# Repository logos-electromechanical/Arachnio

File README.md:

# Arachnio
An Arduino Micro variant with integrated WiFi

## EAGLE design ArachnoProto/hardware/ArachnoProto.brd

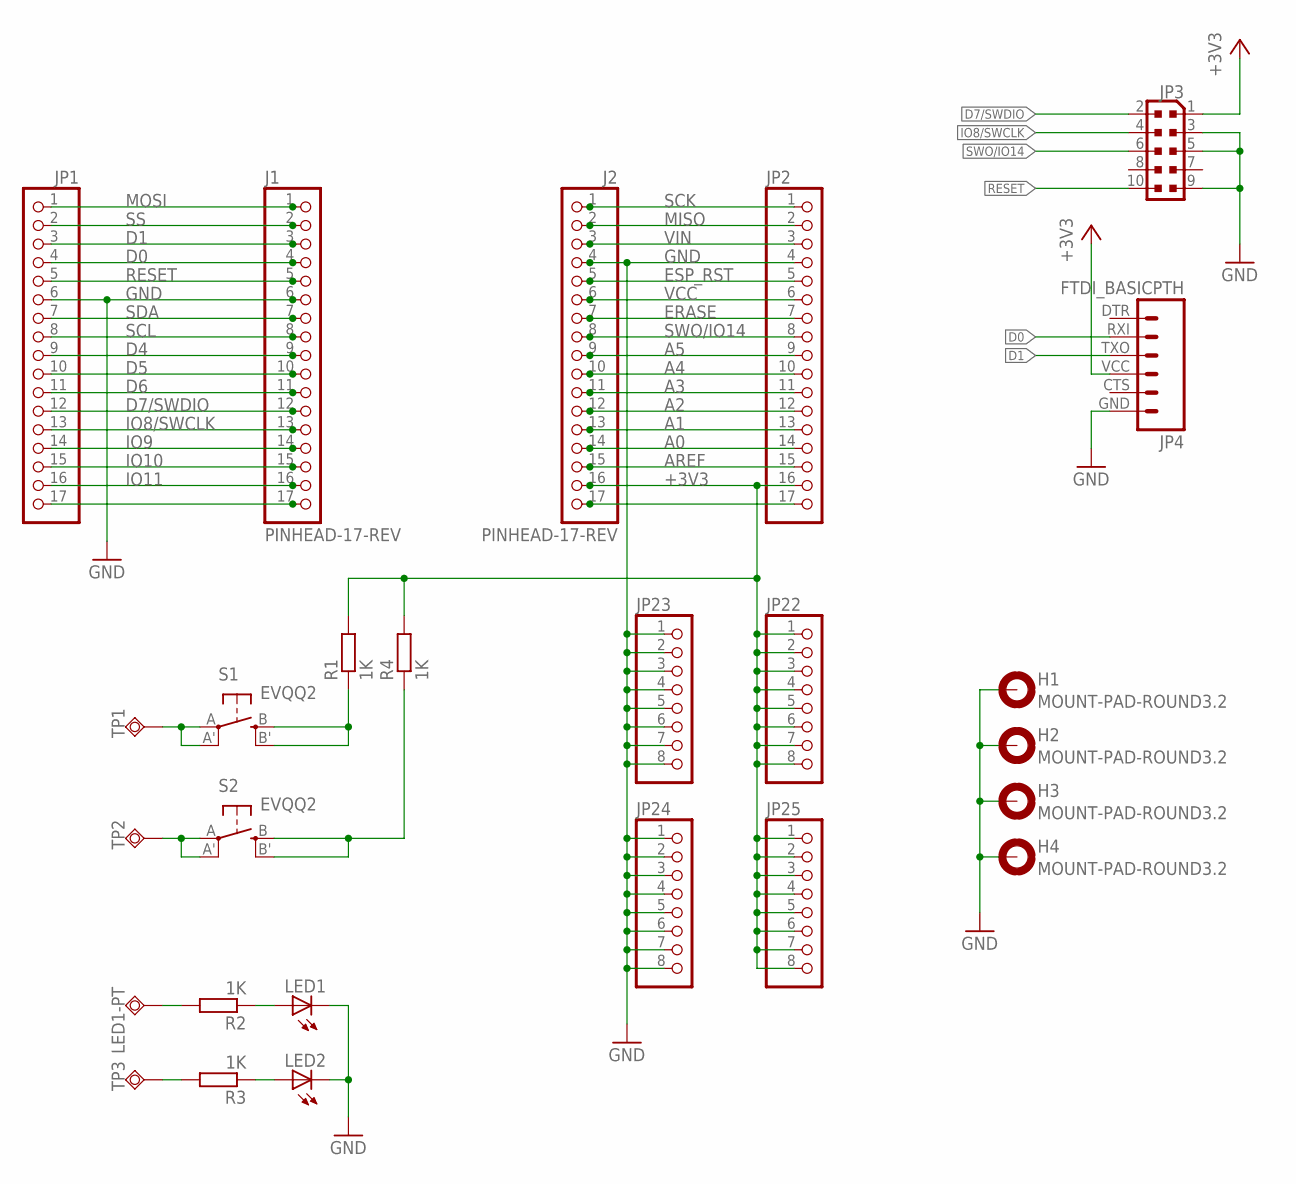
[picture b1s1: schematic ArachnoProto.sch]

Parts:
H1, H2, H3, H4: MOUNT-PAD-ROUND3.2; 3,2-PAD
J1, J2: PINHEAD-17-REV; 4UCONN-12573
JP1, JP2: PINHD-1X17; 1X17
JP3: PINHEAD_PINHD-2X5PASSO127; PINHEAD_2X05_127
JP4: FTDI_BASICPTH; FTDI_BASIC
JP22, JP23, JP24, JP25: PINHD-1X8; 1X08
LED1, LED2: LEDCHIPLED_1206; CHIPLED_1206
LED1-PT: TPSQPAD1-20Y; P1-20Y
R1, R2, R3, R4: 1K; R1206
S1, S2: EVQQ2; EVQ-Q2
TP1, TP2, TP3: TPSQPAD1-20Y; P1-20Y

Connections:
+3V3: J2.16, J2.33, J2.50, JP2.16, JP3.1, JP4.VCC (4), JP22.1, JP22.2, JP22.3, JP22.4, JP22.5, JP22.6, JP22.7, JP22.8, JP25.1, JP25.2, JP25.3, JP25.4, JP25.5, JP25.6, JP25.7, JP25.8, R1.2, R4.2
A0: J2.14, J2.31, J2.48, JP2.14
A1: J2.13, J2.30, J2.47, JP2.13
A2: J2.12, J2.29, J2.46, JP2.12
A3: J2.11, J2.28, J2.45, JP2.11
A4: J2.10, J2.27, J2.44, JP2.10
A5: J2.9, J2.26, J2.43, JP2.9
AREF: J2.15, J2.32, J2.49, JP2.15
D0: J1.4, J1.21, J1.38, JP1.4, JP4.RXI (2)
D1: J1.3, J1.20, J1.37, JP1.3, JP4.TXO (3)
D4: J1.9, J1.26, J1.43, JP1.9
D5: J1.10, J1.27, J1.44, JP1.10
D6: J1.11, J1.28, J1.45, JP1.11
D7/SWDIO: J1.12, J1.29, J1.46, JP1.12, JP3.2
ERASE: J2.7, J2.24, J2.41, JP2.7
ESP_RST: J2.5, J2.22, J2.39, JP2.5
GND: H1.B3,2, H2.B3,2, H3.B3,2, H4.B3,2, J1.6, J1.23, J1.40, J2.4, J2.21, J2.38, JP1.6, JP2.4, JP3.3, JP3.5, JP3.9, JP4.GND (6), JP23.1, JP23.2, JP23.3, JP23.4, JP23.5, JP23.6, JP23.7, JP23.8, JP24.1, JP24.2, JP24.3, JP24.4, JP24.5, JP24.6, JP24.7, JP24.8, LED1.C, LED2.C
IO8/SWCLK: J1.13, J1.30, J1.47, JP1.13, JP3.4
IO9: J1.14, J1.31, J1.48, JP1.14
IO10: J1.15, J1.32, J1.49, JP1.15
IO11: J1.16, J1.33, J1.50, JP1.16
IO12: J1.17, J1.34, J1.51, JP1.17
IO13: J2.17, J2.34, J2.51, JP2.17
MISO: J2.2, J2.19, J2.36, JP2.2
MOSI: J1.1, J1.18, J1.35, JP1.1
unnamed: LED1.A, R2.1
unnamed: LED2.A, R3.1
unnamed: LED1-PT.TP, R2.2
unnamed: R3.2, TP3.TP
unnamed: S1.A, S1.A' (P1), TP1.TP
unnamed: R1.1, S1.B (S), S1.B' (S1)
unnamed: R4.1, S2.B (S), S2.B' (S1)
unnamed: S2.A, S2.A' (P1), TP2.TP
RESET: J1.5, J1.22, J1.39, JP1.5, JP3.10
SCK: J2.1, J2.18, J2.35, JP2.1
SCL: J1.8, J1.25, J1.42, JP1.8
SDA: J1.7, J1.24, J1.41, JP1.7
SS: J1.2, J1.19, J1.36, JP1.2
SWO/IO14: J2.8, J2.25, J2.42, JP2.8, JP3.6
VCC: J2.6, J2.23, J2.40, JP2.6
VIN: J2.3, J2.20, J2.37, JP2.3

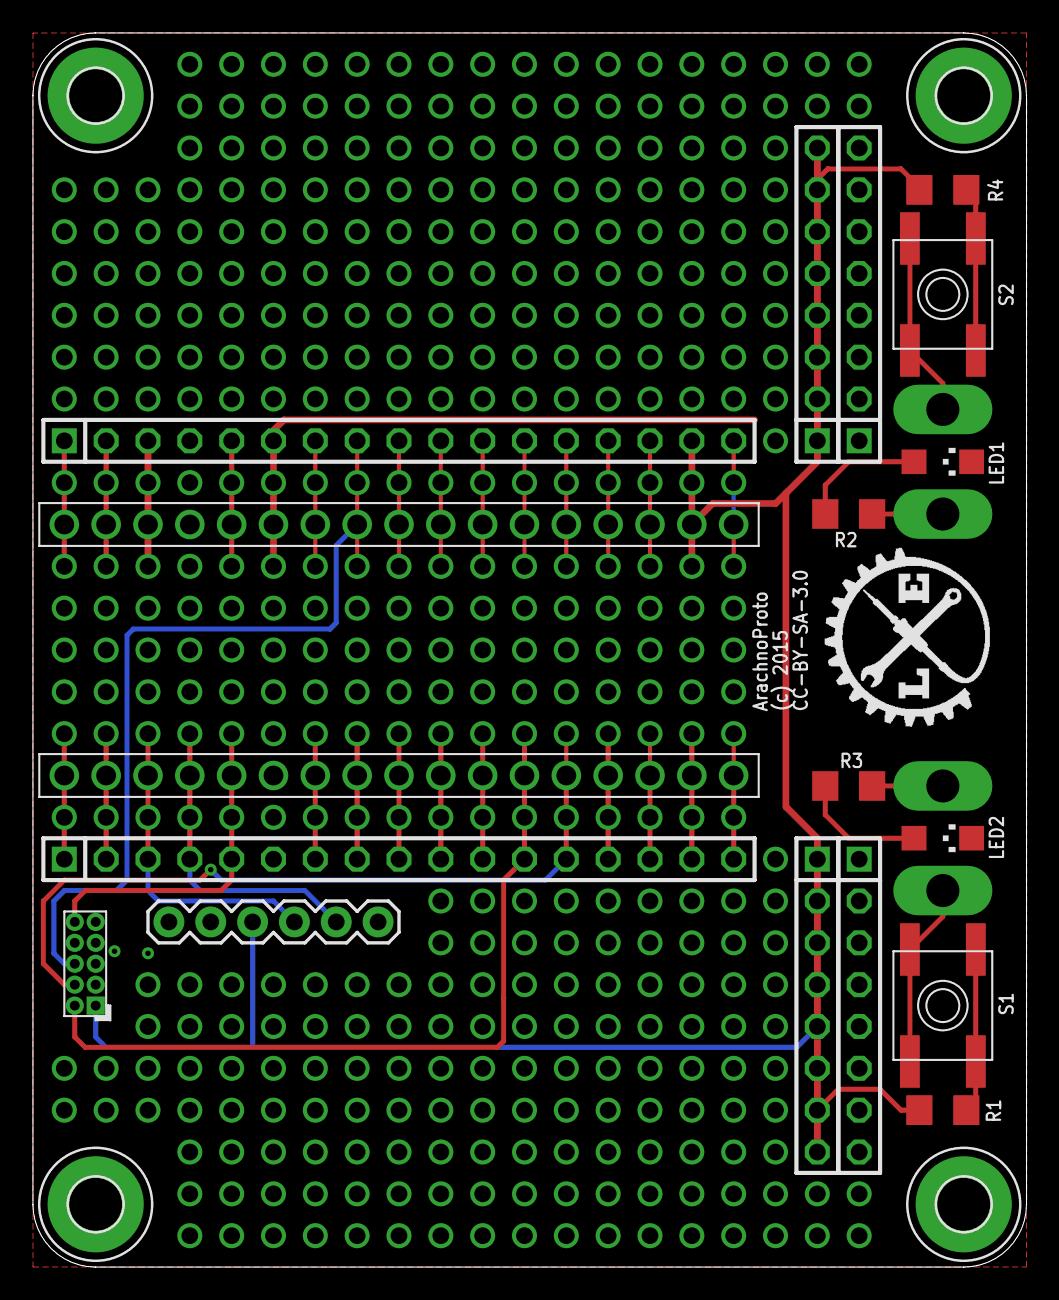
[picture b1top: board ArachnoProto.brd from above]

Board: 2 copper layers, 60.3 x 74.9 mm, 27 parts (0 on the bottom side), 41 nets.

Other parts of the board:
U$1: LOGO-SM

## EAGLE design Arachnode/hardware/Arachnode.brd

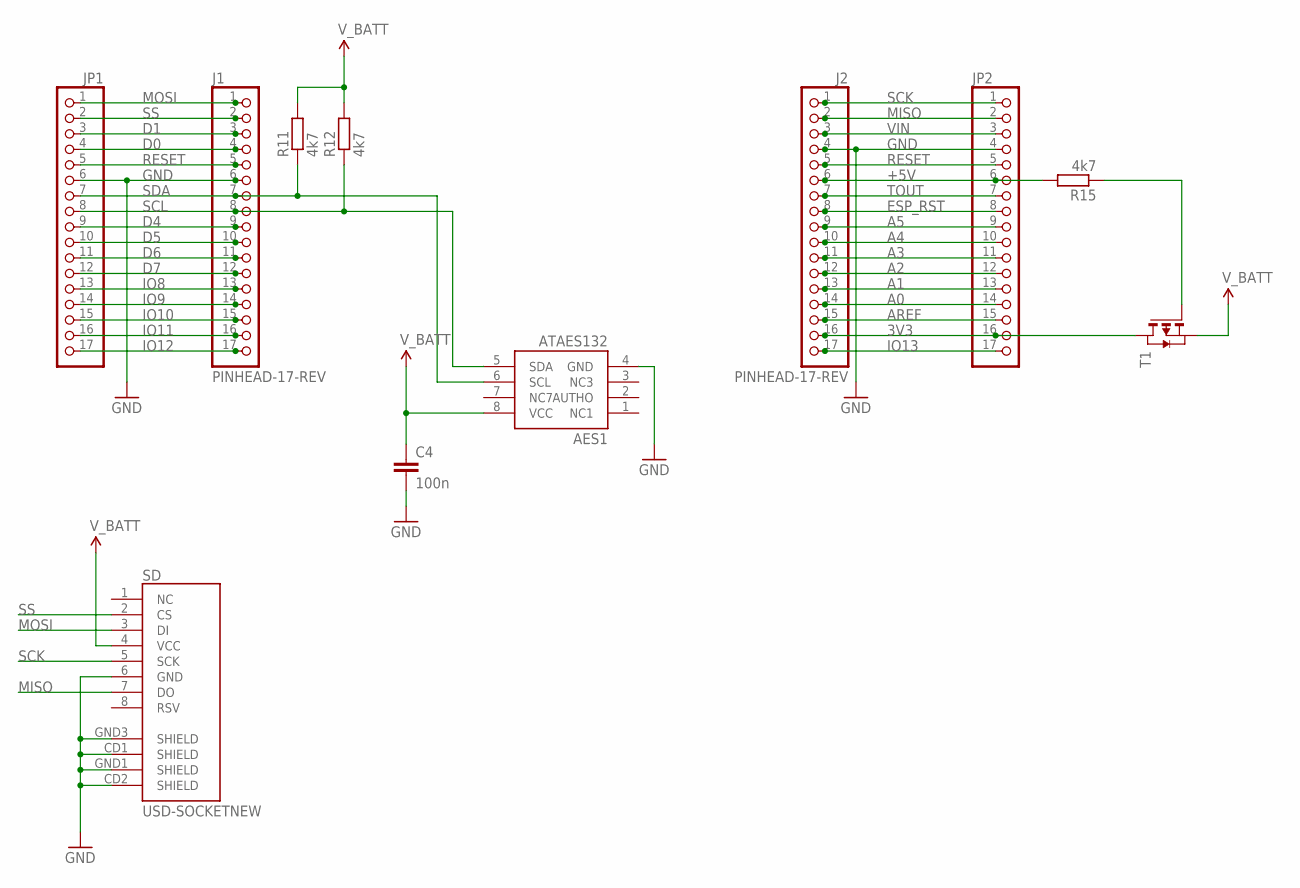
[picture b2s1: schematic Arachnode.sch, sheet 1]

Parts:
AES1: ATAES132; SOIC8
C4: 100n; C0603
J1, J2: PINHEAD-17-REV; 4UCONN-12573
JP1, JP2: PINHD-1X17_2.54; 1X17
R11, R12, R15: 4k7; R0603
SD: USD-SOCKETNEW; MICRO-SD-SOCKET-PP; PARTNO 502570-0893
T1: PMOSSOT23; SOT-23

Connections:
3V3: J2.16, J2.33, J2.50, JP2.16, T1.1 (D)
+5V: J2.6, J2.23, J2.40, JP2.6, R15.2
A0: J2.14, J2.31, J2.48, JP2.14; also elsewhere on the board
A1: J2.13, J2.30, J2.47, JP2.13; also elsewhere on the board
A2: J2.12, J2.29, J2.46, JP2.12
A3: J2.11, J2.28, J2.45, JP2.11
A4: J2.10, J2.27, J2.44, JP2.10
A5: J2.9, J2.26, J2.43, JP2.9
AREF: J2.15, J2.32, J2.49, JP2.15
D0: J1.4, J1.21, J1.38, JP1.4
D1: J1.3, J1.20, J1.37, JP1.3
D4: J1.9, J1.26, J1.43, JP1.9
D5: J1.10, J1.27, J1.44, JP1.10
D6: J1.11, J1.28, J1.45, JP1.11
D7: J1.12, J1.29, J1.46, JP1.12
ESP_RST: J2.8, J2.25, J2.42, JP2.8
GND: AES1.4 (GND), C4.2, J1.6, J1.23, J1.40, J2.4, J2.21, J2.38, JP1.6, JP2.4, SD.6 (GND), SD.CD1 (SHIELD), SD.CD2 (SHIELD), SD.GND1 (SHIELD), SD.GND3 (SHIELD); also elsewhere on the board
IO8: J1.13, J1.30, J1.47, JP1.13
IO9: J1.14, J1.31, J1.48, JP1.14
IO10: J1.15, J1.32, J1.49, JP1.15
IO11: J1.16, J1.33, J1.50, JP1.16
IO12: J1.17, J1.34, J1.51, JP1.17
IO13: J2.17, J2.34, J2.51, JP2.17
MISO: J2.2, J2.19, J2.36, JP2.2, SD.7 (DO)
MOSI: J1.1, J1.18, J1.35, JP1.1, SD.3 (DI)
unnamed: R15.1, T1.3 (G)
RESET: J1.5, J1.22, J1.39, J2.5, J2.22, J2.39, JP1.5, JP2.5
SCK: J2.1, J2.18, J2.35, JP2.1, SD.5 (SCK)
SCL: AES1.5 (SDA), J1.8, J1.25, J1.42, JP1.8, R12.1
SDA: AES1.6 (SCL), J1.7, J1.24, J1.41, JP1.7, R11.1
SS: J1.2, J1.19, J1.36, JP1.2, SD.2 (CS)
TOUT: J2.7, J2.24, J2.41, JP2.7
VIN: J2.3, J2.20, J2.37, JP2.3; also elsewhere on the board
V_BATT: AES1.8 (VCC), C4.1, R11.2, R12.2, SD.4 (VCC), T1.2 (S); also elsewhere on the board

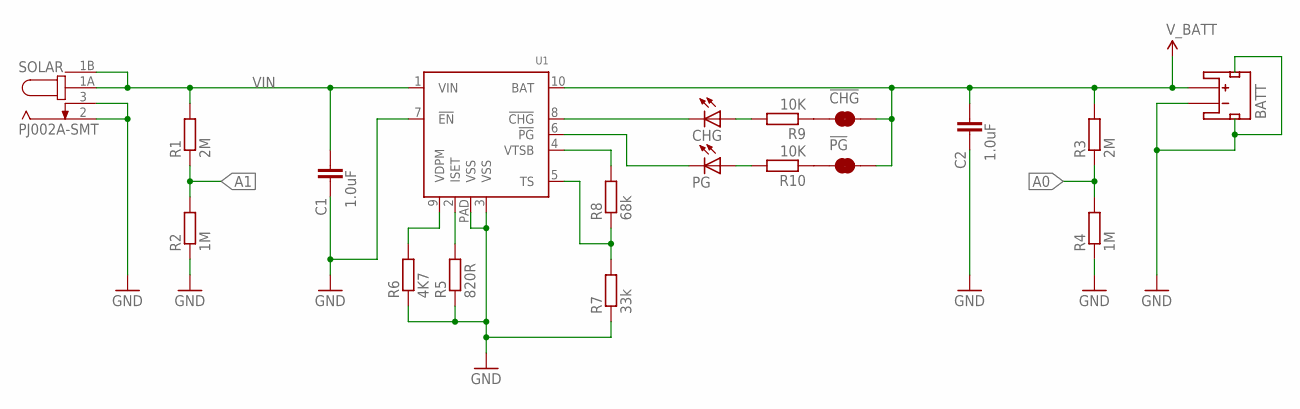
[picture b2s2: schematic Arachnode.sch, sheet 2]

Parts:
!CHG!: JUMPER-PAD-2-NC_BY_TRACE; PAD-JUMPER-2-NC_BY_TRACE_YES_SILK
!PG!: JUMPER-PAD-2-NC_BY_TRACE; PAD-JUMPER-2-NC_BY_TRACE_YES_SILK
BATT: JST_2MM_MALE; JST-2-SMD; PARTNO S2B-PH-SM4-TB(LF)(SN)
C1, C2: 1.0uF; C0603
CHG: LEDCHIP-LED0603; CHIP-LED0603
PG: LEDCHIP-LED0603; CHIP-LED0603
R1, R3: 2M; R0603
R2, R4: 1M; R0603; PARTNO ERJ-3EKF1004V
R5: 820R; R0603
R6: 4K7; R0603
R7: 33k; R0603
R8: 68k; R0603
R9, R10: 10K; R0603
SOLAR: PJ002A-SMT; PARTNO PJ-002AH-SMT
U1: BQ24210; WSON-10

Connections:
A0: R3.1, R4.2; also elsewhere on the board
A1: R1.1, R2.2; also elsewhere on the board
GND: BATT.1 (-), BATT.NC1 (PAD1), BATT.NC2 (PAD2), C1.1, C2.1, R2.1, R4.1, R5.1, R6.1, R7.1, SOLAR.2, SOLAR.3, U1.3 (VSS), U1.7 (!EN!), U1.PAD (VSS); also elsewhere on the board
unnamed: PG.A, R10.2
unnamed: R5.2, U1.2 (ISET)
unnamed: CHG.A, R9.2
unnamed: R6.2, U1.9 (VDPM)
unnamed: R7.2, R8.1, U1.5 (TS)
unnamed: PG.C, U1.6 (!PG!)
unnamed: R8.2, U1.4 (VTSB)
unnamed: CHG.C, U1.8 (!CHG!)
unnamed: !CHG!.1, R9.1
unnamed: !PG!.1, R10.1
VIN: C1.2, R1.2, SOLAR.1A, SOLAR.1B, U1.1 (VIN); also elsewhere on the board
V_BATT: !CHG!.2, !PG!.2, BATT.2 (+), C2.2, R3.2, U1.10 (BAT); also elsewhere on the board

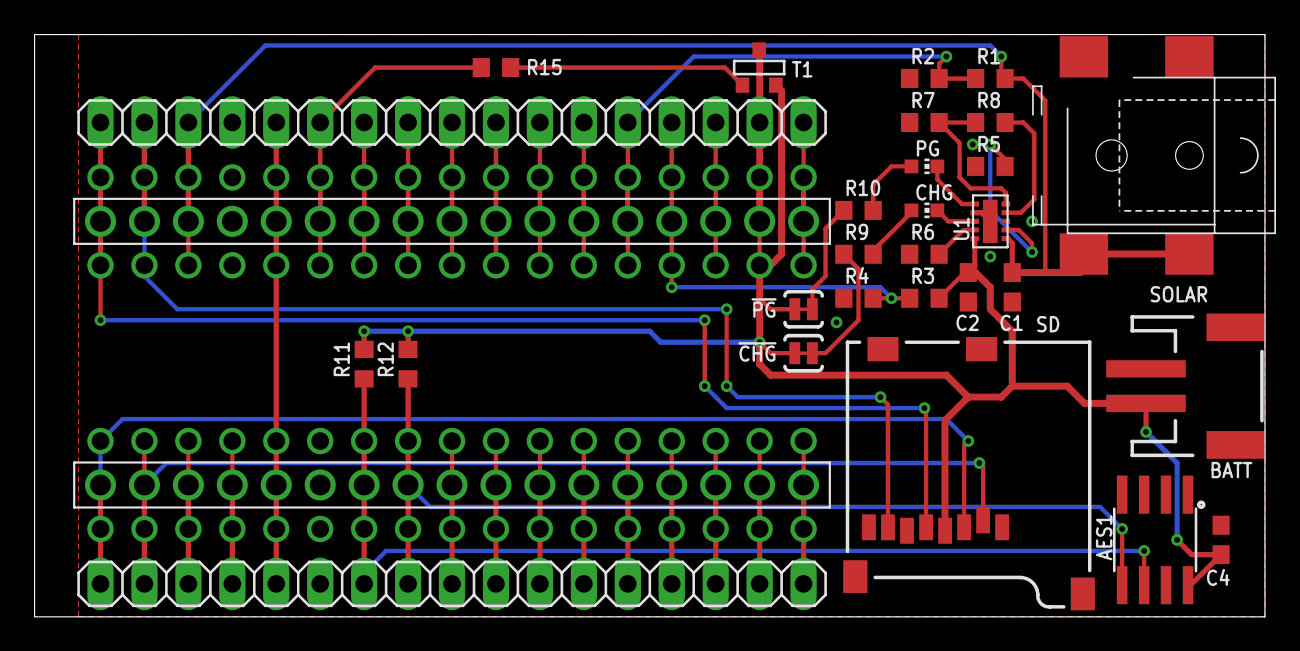
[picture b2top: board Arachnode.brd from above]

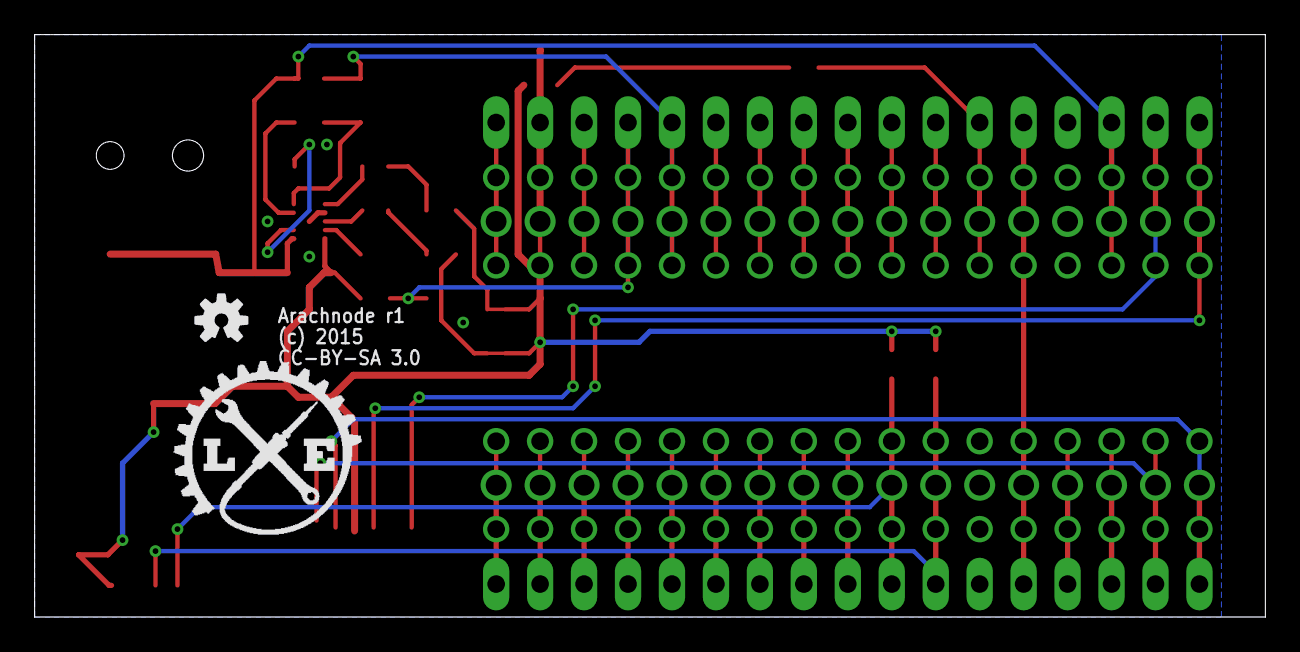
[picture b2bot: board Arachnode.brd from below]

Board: 2 copper layers, 71.1 x 33.7 mm, 32 parts (2 on the bottom side), 44 nets.

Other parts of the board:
U$1: OSHW-LOGO-S
U$2: LOGO-SM

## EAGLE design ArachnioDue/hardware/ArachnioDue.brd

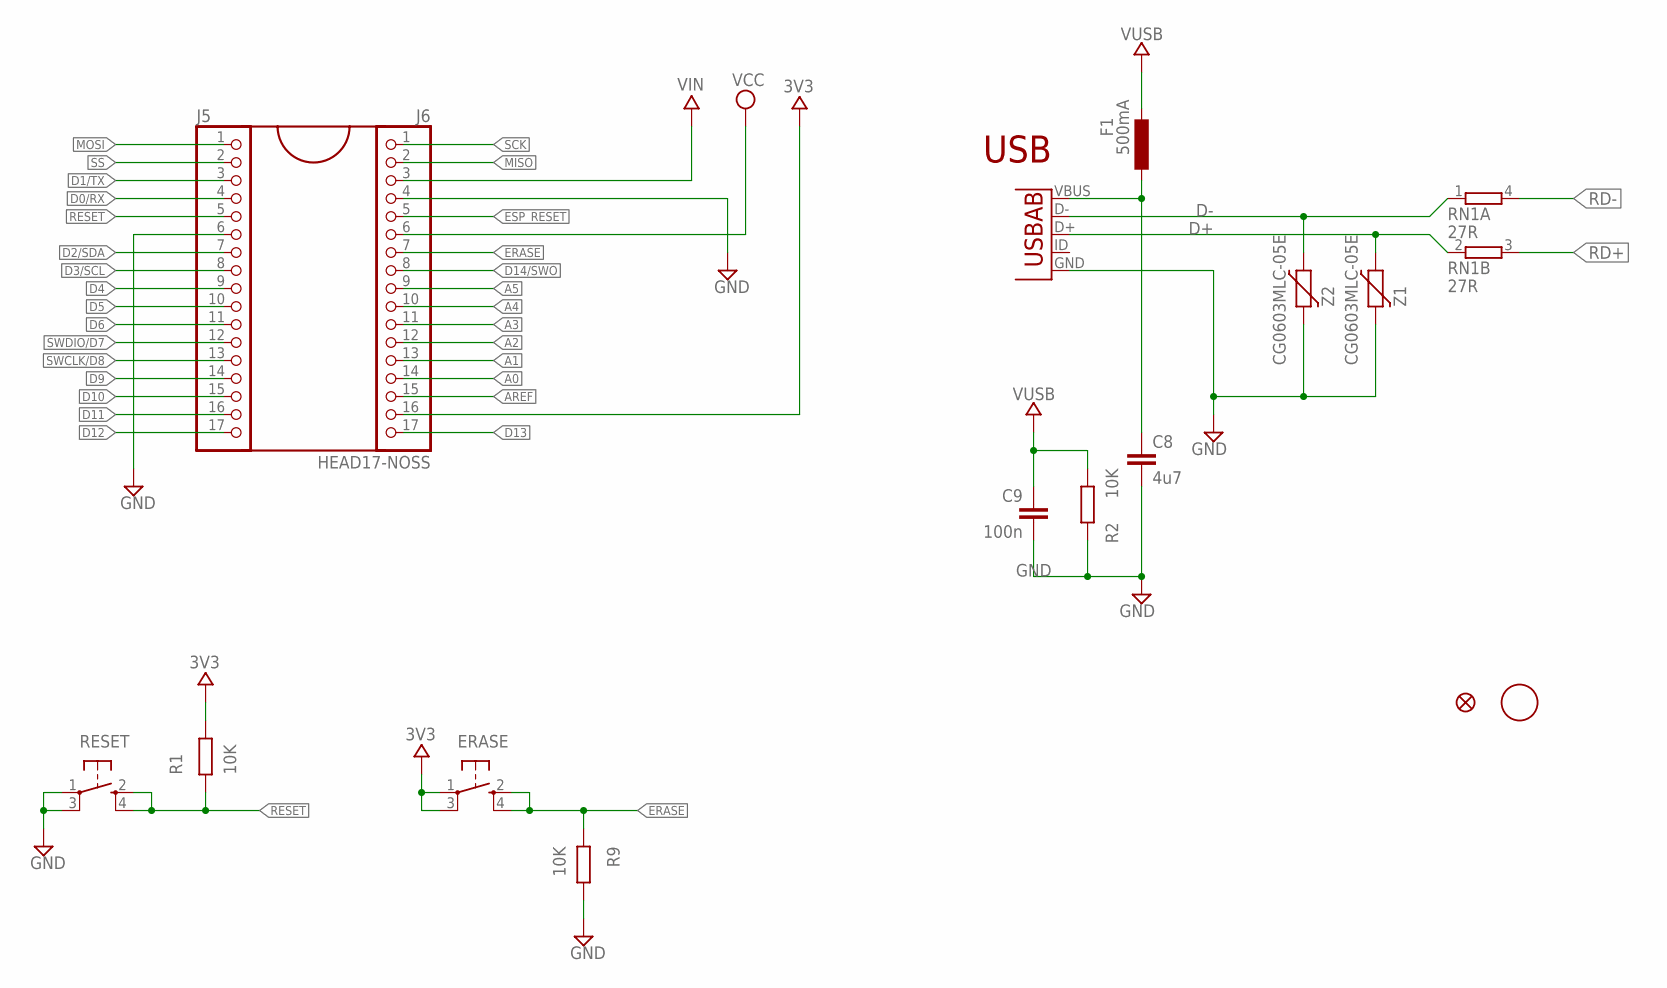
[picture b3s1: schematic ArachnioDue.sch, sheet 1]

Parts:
C8: 4u7; C0603; PARTNO generic MLCC:4u7/25V/0603
C9: 100n; C0603; PARTNO generic MLCC:100n/50V/0603
CN1: USB-AB; USB-AB-MICRO-SMD; PARTNO 10104111-0001LF
ERASE: SPST_TACT-KMR2; KMR2; PARTNO KMR221NG
F1: 500mA; L1812; PARTNO MF-MSMF050-2
J5: PINHD-1X17_2.54-SMD-UNIVERSAL; 1X17SMD-UNIVERSAL; PARTNO PREC017SAAN-RC
J6: HEAD17-NOSS; 1X17SMD-UNIVERSAL; PARTNO PREC017SAAN-RC
R1, R2, R9: 10K; R0402; PARTNO generic resistor:10K/0402
RESET: SPST_TACT-KMR2; KMR2; PARTNO KMR221NG
RN1: 27R; EXBV4V; PARTNO EXB-V4V270JV
U$37: FIDUCIALMOUNT; FIDUCIA-MOUNT
U$53: FIDUCIAL1X2; FIDUCIAL-1X2
Z1, Z2: CG0603MLC-05E; CT/CN0603; PARTNO CG0603MLC-05E

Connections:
3V3: ERASE.1, ERASE.3 (P1), J6.16, R1.1; also elsewhere on the board
A0: J6.14; also elsewhere on the board
A1: J6.13; also elsewhere on the board
A2: J6.12; also elsewhere on the board
A3: J6.11; also elsewhere on the board
A4: J6.10; also elsewhere on the board
A5: J6.9; also elsewhere on the board
AREF: J6.15; also elsewhere on the board
D0/RX: J5.4; also elsewhere on the board
D1/TX: J5.3; also elsewhere on the board
D2/SDA: J5.7; also elsewhere on the board
D3/SCL: J5.8; also elsewhere on the board
D4: J5.9; also elsewhere on the board
D5: J5.10; also elsewhere on the board
D6: J5.11; also elsewhere on the board
D9: J5.14; also elsewhere on the board
D10: J5.15; also elsewhere on the board
D11: J5.16; also elsewhere on the board
D12: J5.17; also elsewhere on the board
D13: J6.17; also elsewhere on the board
D14/SWO: J6.8; also elsewhere on the board
D+: CN1.D+, RN1.2 (1), Z1.1
D-: CN1.D-, RN1.1, Z2.1
ERASE: ERASE.2 (S), ERASE.4 (S1), J6.7, R9.2; also elsewhere on the board
ESP_RESET: J6.5; also elsewhere on the board
GND: C8.2, C9.2, CN1.GND, J5.6, J6.4, R2.1, R9.1, RESET.1, RESET.3 (P1), Z1.2, Z2.2; also elsewhere on the board
MISO: J6.2; also elsewhere on the board
MOSI: J5.1; also elsewhere on the board
RD+: RN1.3 (2); also elsewhere on the board
RD-: RN1.4 (2); also elsewhere on the board
RESET: J5.5, R1.2, RESET.2 (S), RESET.4 (S1); also elsewhere on the board
SCK: J6.1; also elsewhere on the board
SS: J5.2; also elsewhere on the board
SWCLK/D8: J5.13; also elsewhere on the board
SWDIO/D7: J5.12; also elsewhere on the board
VCC: J6.6; also elsewhere on the board
VIN: J6.3; also elsewhere on the board
VUSB: C9.1, F1.2, R2.2; also elsewhere on the board
VUSBD: C8.1, CN1.VBUS, F1.1

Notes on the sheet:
USB

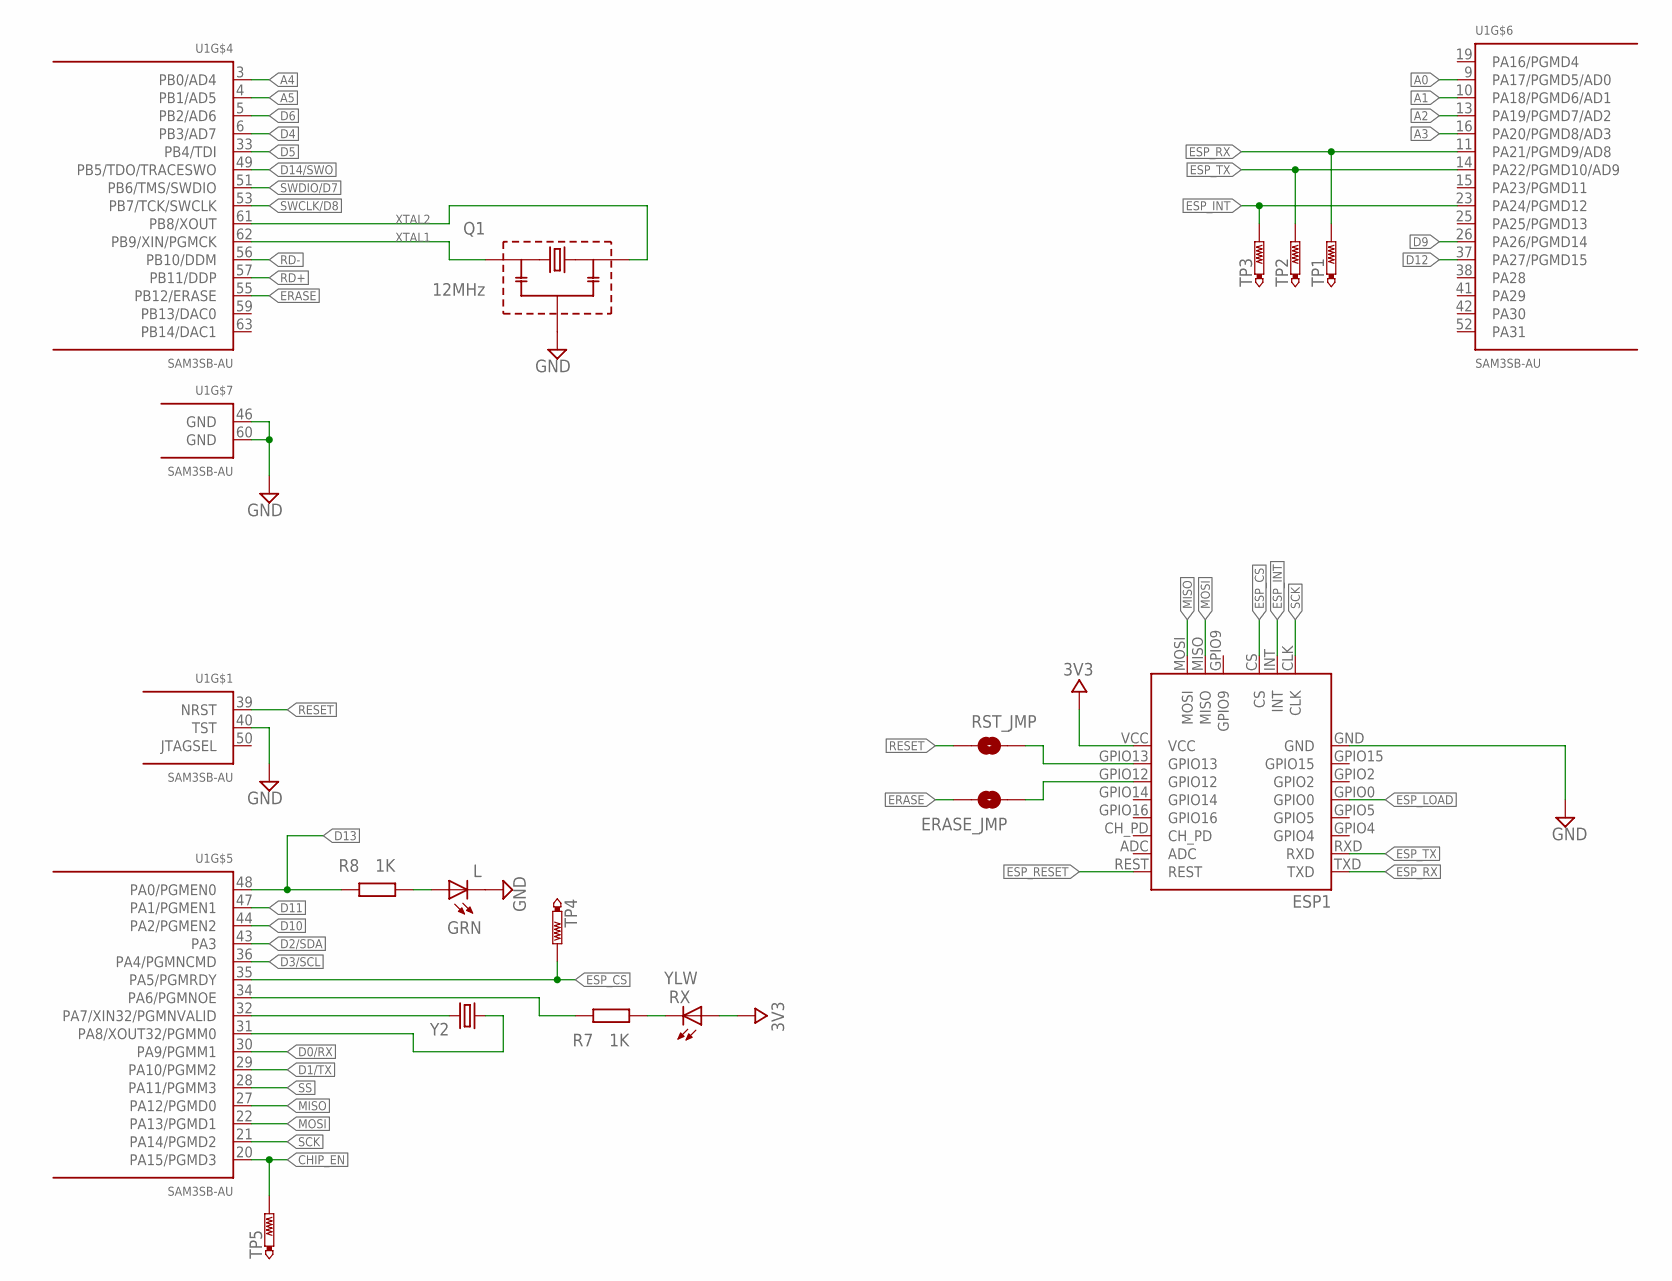
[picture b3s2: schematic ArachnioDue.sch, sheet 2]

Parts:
ERASE_JMP: JUMPER-PAD-2-NOYES_SILK; PAD-JUMPER-2-NO_YES_SILK
ESP1: ESP-12
L: GRN; CHIP-LED0603; PARTNO LTST-C191KGKT
Q1: 12MHz; PRQC; PARTNO PRQC12.00CR1010V00L
R7, R8: 1K; R0402; PARTNO generic resistor:1K/0402
RST_JMP: JUMPER-PAD-2-NOYES_SILK; PAD-JUMPER-2-NO_YES_SILK
RX: YLW; CHIP-LED0603; PARTNO LTST-C191KSKT
TP1, TP2, TP3, TP4, TP5: PTR1TP16R; TP16R
U1: SAM3SB-AU; LQFP64; PARTNO ATSAM4S2AA-MU
Y2: CRYSTALEPSONMC146; CRYSTAL-32KHZ-SMD_EPSON_MC146; PARTNO MC-146 32.768KA-AC3

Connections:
3V3: ESP1.VCC, RX.A; also elsewhere on the board
A0: U1.9 (PA17/PGMD5/AD0); also elsewhere on the board
A1: U1.10 (PA18/PGMD6/AD1); also elsewhere on the board
A2: U1.13 (PA19/PGMD7/AD2); also elsewhere on the board
A3: U1.16 (PA20/PGMD8/AD3); also elsewhere on the board
A4: U1.3 (PB0/AD4); also elsewhere on the board
A5: U1.4 (PB1/AD5); also elsewhere on the board
CHIP_EN: TP5.TP, U1.20 (PA15/PGMD3)
D0/RX: U1.30 (PA9/PGMM1); also elsewhere on the board
D1/TX: U1.29 (PA10/PGMM2); also elsewhere on the board
D2/SDA: U1.43 (PA3); also elsewhere on the board
D3/SCL: U1.36 (PA4/PGMNCMD); also elsewhere on the board
D4: U1.6 (PB3/AD7); also elsewhere on the board
D5: U1.33 (PB4/TDI); also elsewhere on the board
D6: U1.5 (PB2/AD6); also elsewhere on the board
D9: U1.26 (PA26/PGMD14); also elsewhere on the board
D10: U1.44 (PA2/PGMEN2); also elsewhere on the board
D11: U1.47 (PA1/PGMEN1); also elsewhere on the board
D12: U1.37 (PA27/PGMD15); also elsewhere on the board
D13: R8.1, U1.48 (PA0/PGMEN0); also elsewhere on the board
D14/SWO: U1.49 (PB5/TDO/TRACESWO); also elsewhere on the board
ERASE: ERASE_JMP.2, U1.55 (PB12/ERASE); also elsewhere on the board
ESP_CS: ESP1.CS, TP4.TP, U1.35 (PA5/PGMRDY)
ESP_INT: ESP1.INT, TP3.TP, U1.23 (PA24/PGMD12)
ESP_LOAD: ESP1.GPIO0
ESP_RESET: ESP1.REST; also elsewhere on the board
ESP_RX: ESP1.TXD, TP1.TP, U1.11 (PA21/PGMD9/AD8)
ESP_TX: ESP1.RXD, TP2.TP, U1.14 (PA22/PGMD10/AD9)
GND: ESP1.GND, L.C, Q1.P$2 (2), U1.40 (TST), U1.46 (GND), U1.60 (GND); also elsewhere on the board
MISO: ESP1.MOSI, U1.27 (PA12/PGMD0); also elsewhere on the board
MOSI: ESP1.MISO, U1.22 (PA13/PGMD1); also elsewhere on the board
unnamed: U1.31 (PA8/XOUT32/PGMM0), Y2.P$2 (1)
unnamed: R7.2, RX.C
unnamed: ESP1.GPIO13, RST_JMP.2
unnamed: U1.32 (PA7/XIN32/PGMNVALID), Y2.P$1 (2)
unnamed: L.A, R8.2
unnamed: ERASE_JMP.1, ESP1.GPIO12
RD+: U1.57 (PB11/DDP); also elsewhere on the board
RD-: U1.56 (PB10/DDM); also elsewhere on the board
RESET: RST_JMP.1, U1.39 (NRST); also elsewhere on the board
RXTXLED: R7.1, U1.34 (PA6/PGMNOE)
SCK: ESP1.CLK, U1.21 (PA14/PGMD2); also elsewhere on the board
SS: U1.28 (PA11/PGMM3); also elsewhere on the board
SWCLK/D8: U1.53 (PB7/TCK/SWCLK); also elsewhere on the board
SWDIO/D7: U1.51 (PB6/TMS/SWDIO); also elsewhere on the board
XTAL1: Q1.P$3 (3), U1.62 (PB9/XIN/PGMCK)
XTAL2: Q1.P$1 (1), U1.61 (PB8/XOUT)

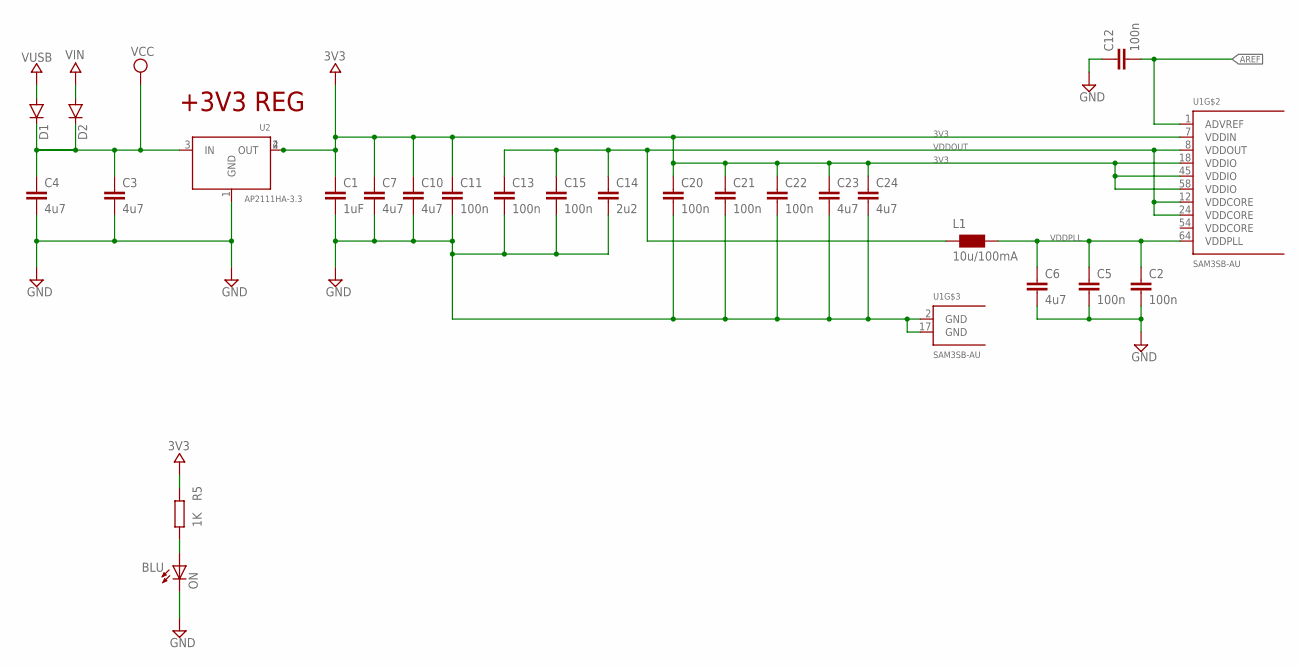
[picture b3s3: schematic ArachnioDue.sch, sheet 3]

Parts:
C1: 1uF; C0603; PARTNO generic MLCC:1u/25V/0603
C2, C12: 100n; C0402; PARTNO generic MLCC:100n/16V/0402
C3, C4: 4u7; C0603; PARTNO generic MLCC:4u7/25V/0603
C5, C11, C13, C15, C20, C21, C22: 100n; C0402; VOLTAGE 16V; PARTNO generic MLCC:100n/16V/0402
C6, C7, C10, C23, C24: 4u7; C0603; VOLTAGE 10V; PARTNO generic MLCC:4u7/10V/0603
C14: 2u2; C0603; VOLTAGE 6V3; PARTNO generic MLCC:2u2/6V3/0603
D1, D2: DIODESOD123; SOD-123; PARTNO CDBW140-G
L1: 10u/100mA; 0805; PARTNO MLZ2012N100LT000
ON: BLU; CHIP-LED0603; PARTNO LB Q39G-L2N2-35-1
R5: 1K; R0402; PARTNO generic resistor:1K/0402
U1: SAM3SB-AU; LQFP64; PARTNO ATSAM4S2AA-MU
U2: AP2111HA-3.3; SOT223; PARTNO AP2111H-3.3TRG1

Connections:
3V3: C1.1, C7.1, C10.1, C11.1, C20.1, C21.1, C22.1, C23.1, C24.1, R5.1, U1.7 (VDDIN), U1.18 (VDDIO), U1.45 (VDDIO), U1.58 (VDDIO), U2.2 (OUT), U2.4 (OUT); also elsewhere on the board
AREF: C12.2, U1.1 (ADVREF); also elsewhere on the board
GND: C1.2, C2.2, C3.2, C4.2, C5.2, C6.2, C7.2, C10.2, C11.2, C12.1, C13.2, C14.2, C15.2, C20.2, C21.2, C22.2, C23.2, C24.2, ON.C, U1.2 (GND), U1.17 (GND), U2.1 (GND); also elsewhere on the board
unnamed: ON.A, R5.2
VCC: C3.1, C4.1, D1.C, D2.C, U2.3 (IN); also elsewhere on the board
VDDOUT: C13.1, C14.1, C15.1, L1.1, U1.8 (VDDOUT), U1.12 (VDDCORE), U1.24 (VDDCORE)
VDDPLL: C2.1, C5.1, C6.1, L1.2, U1.64 (VDDPLL)
VIN: D2.A; also elsewhere on the board
VUSB: D1.A; also elsewhere on the board

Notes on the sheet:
+3V3 REG

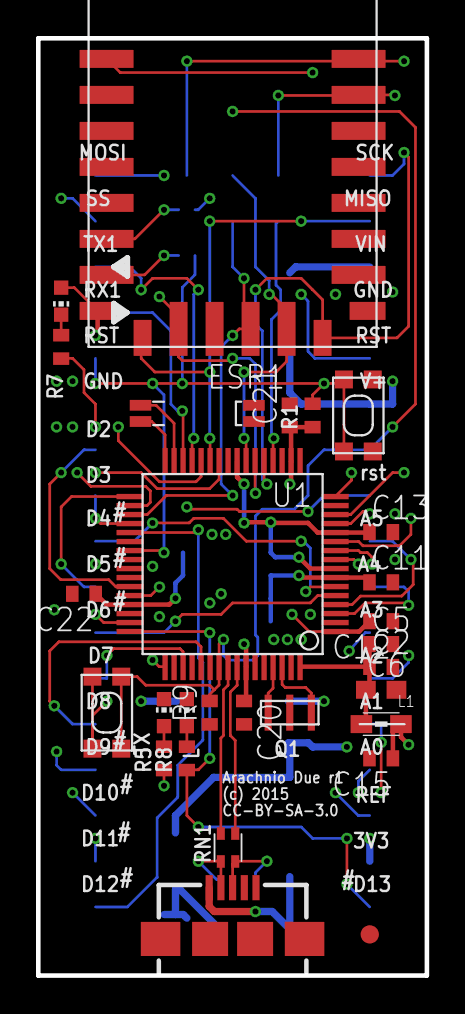
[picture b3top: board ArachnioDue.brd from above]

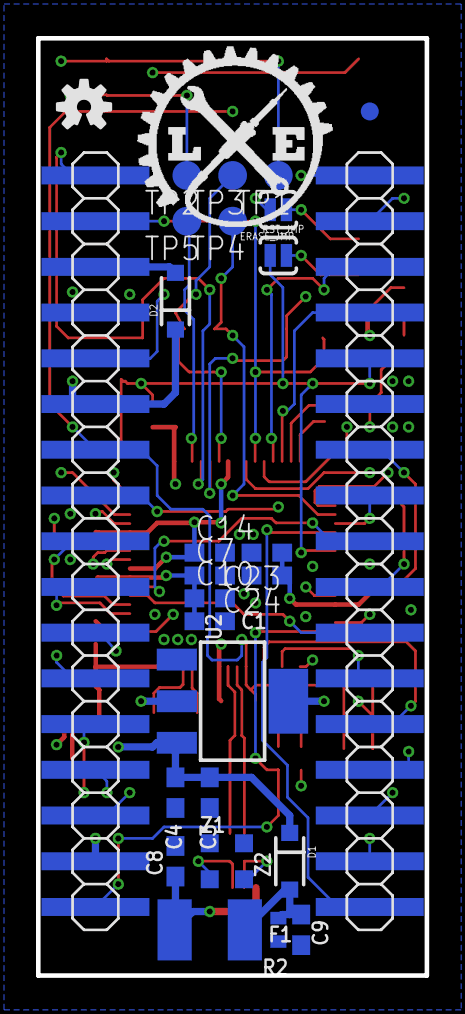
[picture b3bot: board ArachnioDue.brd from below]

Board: 4 copper layers, 21.6 x 52.1 mm, 57 parts (29 on the bottom side), 56 nets.

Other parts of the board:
U$1: LOGO-SM
U$12: OSHW-LOGO-S

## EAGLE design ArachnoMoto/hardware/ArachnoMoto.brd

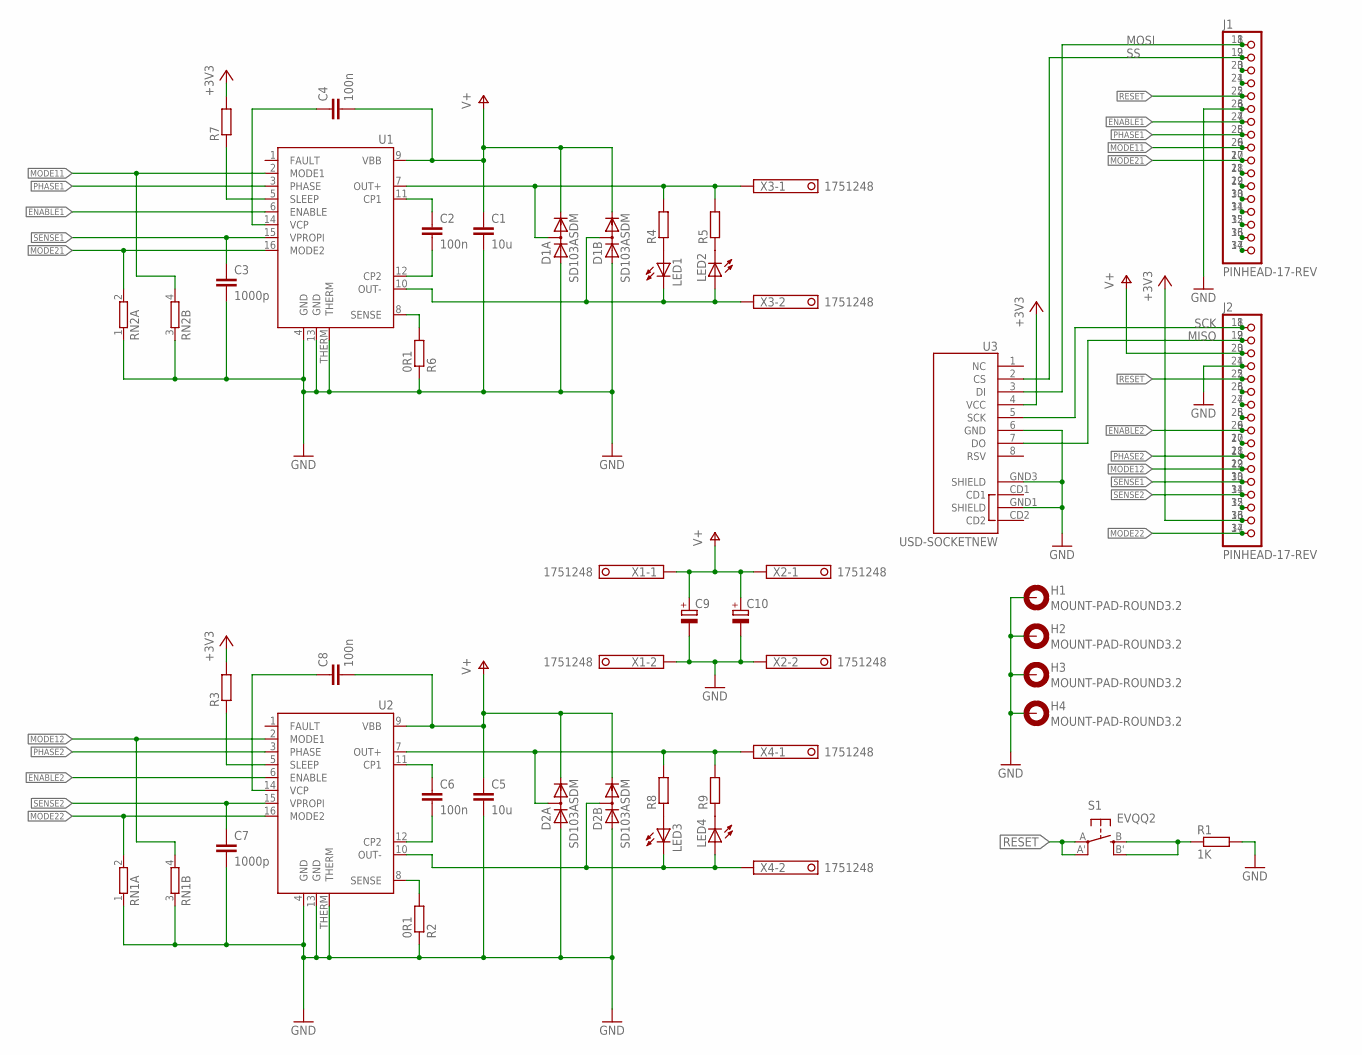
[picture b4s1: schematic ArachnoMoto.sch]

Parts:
C1, C5: 10u; C1210
C2, C4, C6, C8: 100n; C0603
C3, C7: 1000p; C0603
C9, C10: CPOL-EUE5-10.5; E5-10,5
D1, D2: SD103ASDM; SOT26
H1, H2, H3, H4: MOUNT-PAD-ROUND3.2; 3,2-PAD
J1, J2: PINHEAD-17-REV; 4UCONN-12573
LED1, LED2, LED3, LED4: LEDCHIP-LED0603; CHIP-LED0603
R1: 1K; R1206
R2, R6: 0R1; R1206
R3, R4, R5, R7, R8, R9: R-EU_R0603; R0603
RN1, RN2: 4R-NCTS742C083; CTS742C083-RES
S1: EVQQ2; EVQ-Q2
U1, U2: DRV8801; HTSSOP16-PWP
U3: USD-SOCKETNEW; MICRO-SD-SOCKET-PP
X1, X2, X3, X4: 1751248

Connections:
+3V3: J2.16, J2.33, R3.2, R7.2, U3.4 (VCC)
AREF: J2.15, J2.32
D0: J1.4, J1.21
D1: J1.3, J1.20
D6: J1.11, J1.28
D7/SWDIO: J1.12, J1.29
ENABLE1: J1.7, J1.24, U1.6 (ENABLE)
ENABLE2: J2.9, J2.26, U2.6 (ENABLE)
ESP_RST: J2.8, J2.25
GND: C1.2, C3.2, C5.2, C7.2, C9.-, C10.-, D1.3 (A), D1.6 (A), D2.3 (A), D2.6 (A), H1.B3,2, H2.B3,2, H3.B3,2, H4.B3,2, J1.6, J1.23, J2.4, J2.21, R1.2, R2.1, R6.1, RN1.1, RN1.3 (1), RN2.1, RN2.3 (1), U1.4 (GND), U1.13 (GND), U1.THERM, U2.4 (GND), U2.13 (GND), U2.THERM, U3.6 (GND), U3.GND1 (SHIELD), U3.GND3 (SHIELD), X1.2, X2.2
IO8/SWCLK: J1.13, J1.30
IO9: J1.14, J1.31
IO10: J1.15, J1.32
IO11: J1.16, J1.33
MISO: J2.2, J2.19, U3.7 (DO)
MODE11: J1.9, J1.26, RN2.4 (2), U1.2 (MODE1)
MODE12: J2.12, J2.29, RN1.4 (2), U2.2 (MODE1)
MODE21: J1.10, J1.27, RN2.2, U1.16 (MODE2)
MODE22: J2.17, J2.34, RN1.2, U2.16 (MODE2)
MOSI: J1.1, J1.18, U3.3 (DI)
unnamed: D2.4 (AC), R8.2, R9.2, U2.7 (OUT+), X4.1
unnamed: J1.17, J1.34
unnamed: D2.1 (AC), LED3.C, LED4.A, U2.10 (OUT-), X4.2
unnamed: LED1.A, R4.1
unnamed: C6.2, U2.12 (CP2)
unnamed: C6.1, U2.11 (CP1)
unnamed: R2.2, U2.8 (SENSE)
unnamed: R1.1, S1.B (S), S1.B' (S1)
unnamed: C8.1, U2.14 (VCP)
unnamed: J2.6, J2.23
unnamed: LED2.C, R5.1
unnamed: LED3.A, R8.1
unnamed: R3.1, U2.5 (SLEEP)
unnamed: LED4.C, R9.1
unnamed: D1.4 (AC), R4.2, R5.2, U1.7 (OUT+), X3.1
unnamed: D1.1 (AC), LED1.C, LED2.A, U1.10 (OUT-), X3.2
unnamed: C2.2, U1.12 (CP2)
unnamed: C2.1, U1.11 (CP1)
unnamed: R6.2, U1.8 (SENSE)
unnamed: C4.1, U1.14 (VCP)
unnamed: R7.1, U1.5 (SLEEP)
NC: J2.10, J2.27
PHASE1: J1.8, J1.25, U1.3 (PHASE)
PHASE2: J2.11, J2.28, U2.3 (PHASE)
RESET: J1.5, J1.22, J2.5, J2.22, S1.A, S1.A' (P1)
SCK: J2.1, J2.18, U3.5 (SCK)
SENSE1: C3.1, J2.13, J2.30, U1.15 (VPROPI)
SENSE2: C7.1, J2.14, J2.31, U2.15 (VPROPI)
SS: J1.2, J1.19, U3.2 (CS)
TOUT: J2.7, J2.24
V+: C1.1, C4.2, C5.1, C8.2, C9.+, C10.+, D1.2 (C), D1.5 (C), D2.2 (C), D2.5 (C), J2.3, J2.20, U1.9 (VBB), U2.9 (VBB), X1.1, X2.1

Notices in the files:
Arachnio/hardware/Arachnio.brd:
(c) 2015
CC-BY-SA-3.0
parts and their libraries:
SparkFun-Passives: Licensing: Creative Commons ShareAlike 4.0 International - https://creativecommons.org/licenses/by-sa/4.0
SparkFun-Aesthetics: Licensing: CC v3.0 Share-Alike You are welcome to use this library for commercial purposes.
